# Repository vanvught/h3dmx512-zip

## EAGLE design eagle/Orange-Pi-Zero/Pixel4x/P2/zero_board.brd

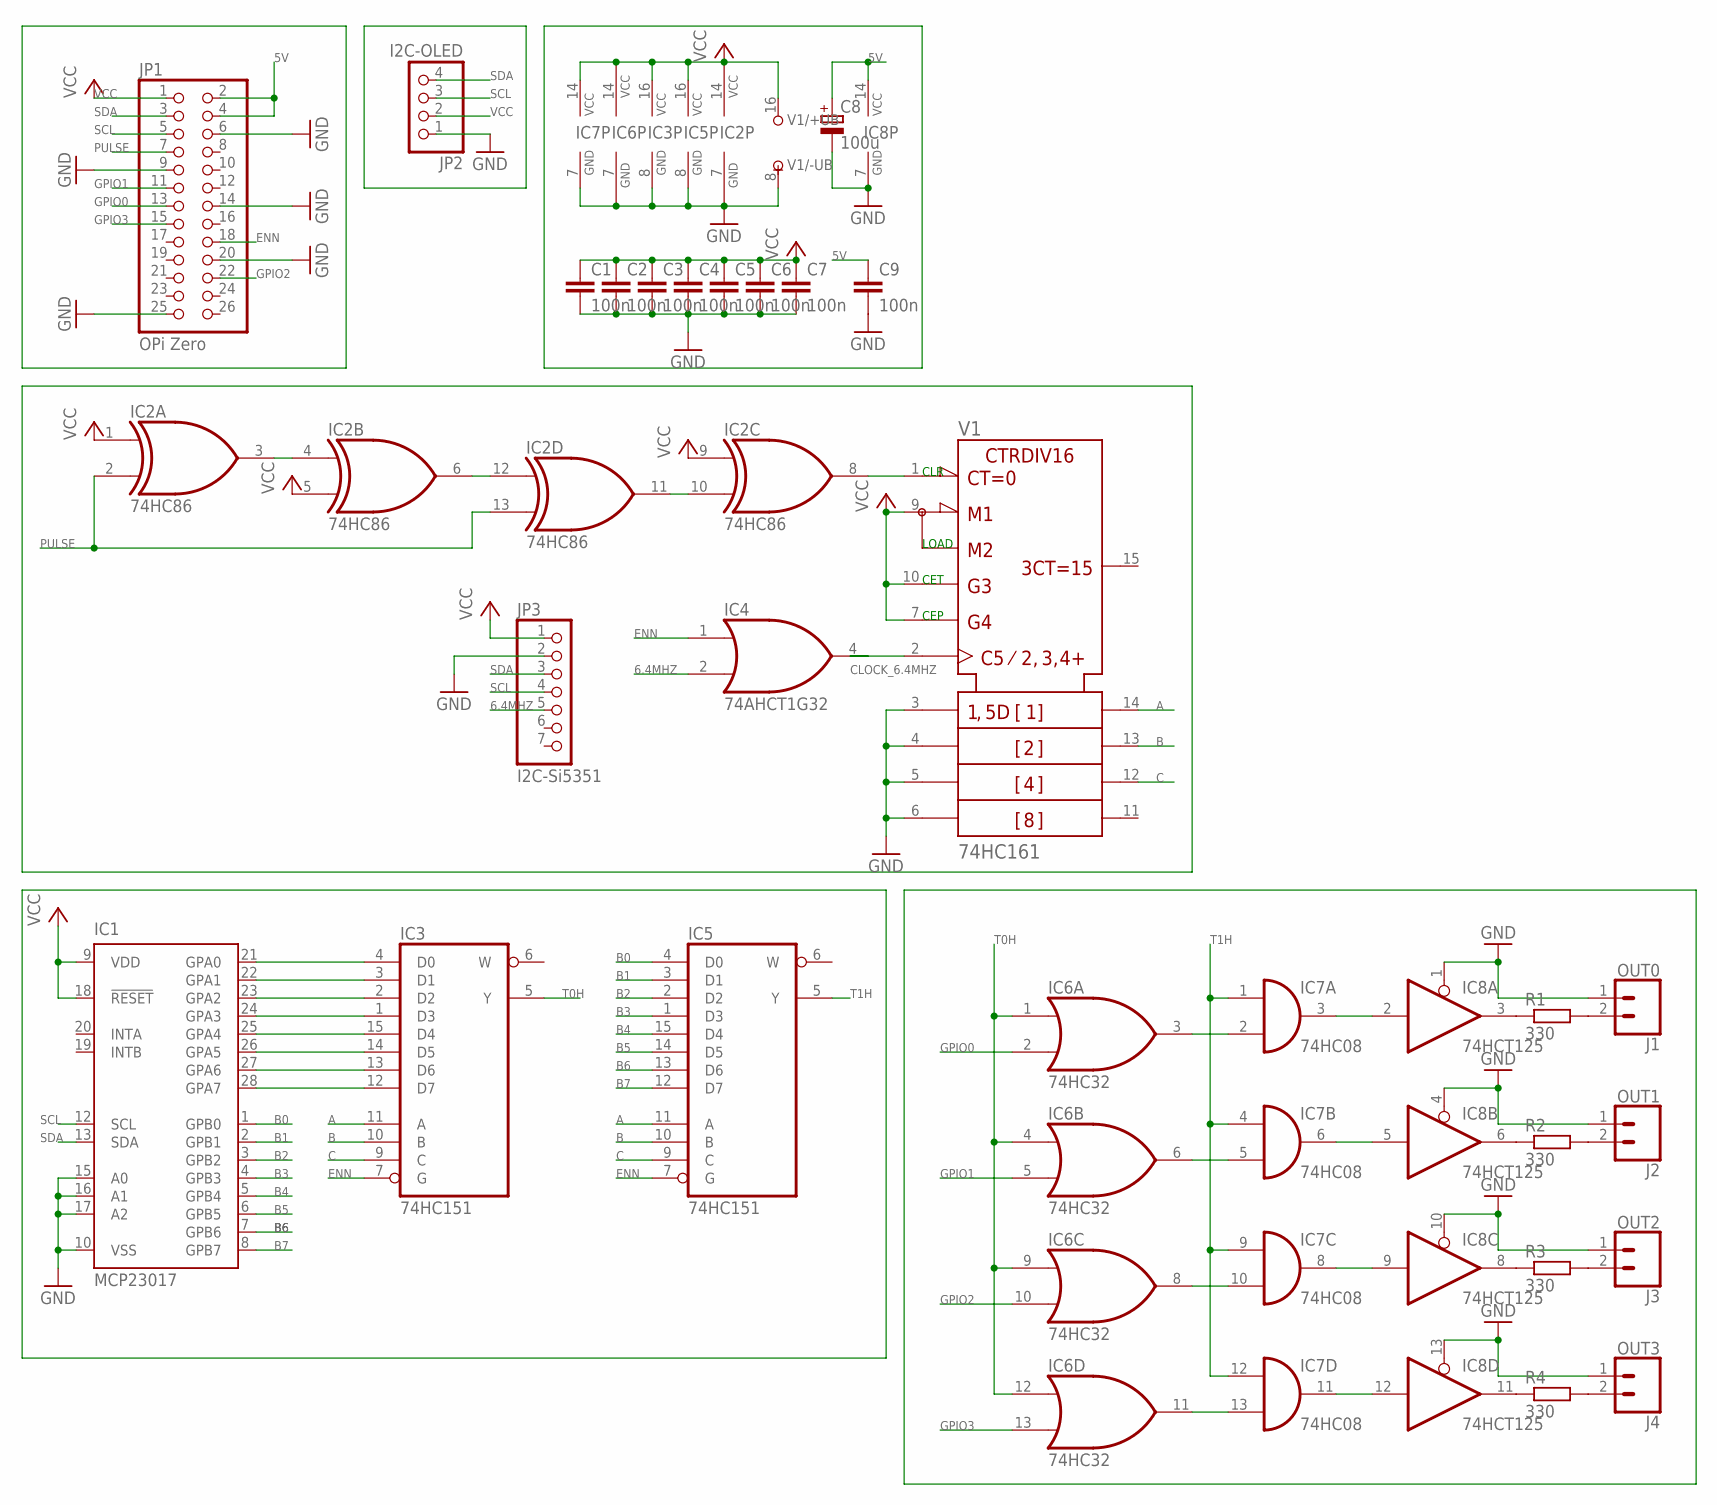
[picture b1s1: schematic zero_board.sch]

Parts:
C1, C2, C3, C4, C5, C6, C7, C9: 100n; C050-024X044
C8: 100u; E2,5-6
IC1: MCP23017; DIL28-3
IC2: 74HC86; DIL14
IC3, IC5: 74HC151; DIL16
IC4: 74AHCT1G32; SOT23-5
IC6: 74HC32; DIL14
IC7: 74HC08; DIL14
IC8: 74HCT125; DIL14
J1: OUT0; SCREWTERMINAL-3.5MM-2
J2: OUT1; SCREWTERMINAL-3.5MM-2
J3: OUT2; SCREWTERMINAL-3.5MM-2
J4: OUT3; SCREWTERMINAL-3.5MM-2
JP1: OPi Zero; 2X13
JP2: I2C-OLED; 1X04
JP3: I2C-Si5351; 1X07
R1, R2, R3, R4: 330; 0204/5
V1: 74HC161; DIL16

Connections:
5V: C8.+, C9.1, IC8.14 (VCC), JP1.2, JP1.4
6.4MHZ: IC4.2 (I1), JP3.5
A: IC3.11 (A), IC5.11 (A), V1.14 (QA)
B: IC3.10 (B), IC5.10 (B), V1.13 (QB)
B0: IC1.1 (GPB0), IC5.4 (D0)
B1: IC1.2 (GPB1), IC5.3 (D1)
B2: IC1.3 (GPB2), IC5.2 (D2)
B3: IC1.4 (GPB3), IC5.1 (D3)
B4: IC1.5 (GPB4), IC5.15 (D4)
B5: IC1.6 (GPB5), IC5.14 (D5)
B6: IC1.7 (GPB6), IC5.13 (D6)
B7: IC1.8 (GPB7), IC5.12 (D7)
C: IC3.9 (C), IC5.9 (C), V1.12 (QC)
CLOCK_6.4MHZ: IC4.4 (O), V1.2 (CLK)
ENN: IC3.7 (G), IC4.1 (I0), IC5.7 (G), JP1.18
GND: C1.2, C2.2, C3.2, C4.2, C5.2, C6.2, C7.2, C8.-, C9.2, IC1.10 (VSS), IC1.15 (A0), IC1.16 (A1), IC1.17 (A2), IC2.7 (GND), IC3.8 (GND), IC4.3 (GND), IC5.8 (GND), IC6.7 (GND), IC7.7 (GND), IC8.1 (OE), IC8.4 (OE), IC8.7 (GND), IC8.10 (OE), IC8.13 (OE), J1.1, J2.1, J3.1, J4.1, JP1.6, JP1.9, JP1.14, JP1.20, JP1.25, JP2.1, JP3.2, V1.3 (A), V1.4 (B), V1.5 (C), V1.6 (D), V1.8 (-UB)
GPIO0: IC6.2 (I1), JP1.13
GPIO1: IC6.5 (I1), JP1.11
GPIO2: IC6.10 (I1), JP1.22
GPIO3: IC6.13 (I1), JP1.15
unnamed: IC2.3 (O), IC2.4 (I0)
unnamed: IC2.6 (O), IC2.12 (I0)
unnamed: IC2.10 (I1), IC2.11 (O)
unnamed: IC2.8 (O), V1.1 (!CLR)
unnamed: IC6.3 (O), IC7.2 (I1)
unnamed: IC6.6 (O), IC7.5 (I1)
unnamed: IC1.21 (GPA0), IC3.4 (D0)
unnamed: IC1.22 (GPA1), IC3.3 (D1)
unnamed: IC1.23 (GPA2), IC3.2 (D2)
unnamed: IC1.24 (GPA3), IC3.1 (D3)
unnamed: IC1.25 (GPA4), IC3.15 (D4)
unnamed: IC1.26 (GPA5), IC3.14 (D5)
unnamed: IC1.27 (GPA6), IC3.13 (D6)
unnamed: IC1.28 (GPA7), IC3.12 (D7)
unnamed: IC6.8 (O), IC7.10 (I1)
unnamed: IC6.11 (O), IC7.13 (I1)
unnamed: IC7.11 (O), IC8.12 (I)
unnamed: IC7.8 (O), IC8.9 (I)
unnamed: IC7.6 (O), IC8.5 (I)
unnamed: IC7.3 (O), IC8.2 (I)
unnamed: IC8.3 (O), R1.1
unnamed: J1.2, R1.2
unnamed: IC8.6 (O), R2.1
unnamed: J2.2, R2.2
unnamed: IC8.8 (O), R3.1
unnamed: J3.2, R3.2
unnamed: IC8.11 (O), R4.1
unnamed: J4.2, R4.2
PULSE: IC2.2 (I1), IC2.13 (I1), JP1.7
SCL: IC1.12 (SCL), JP1.5, JP2.3, JP3.4
SDA: IC1.13 (SDA), JP1.3, JP2.4, JP3.3
T0H: IC3.5 (Y), IC6.1 (I0), IC6.4 (I0), IC6.9 (I0), IC6.12 (I0)
T1H: IC5.5 (Y), IC7.1 (I0), IC7.4 (I0), IC7.9 (I0), IC7.12 (I0)
VCC: C1.1, C2.1, C3.1, C4.1, C5.1, C6.1, C7.1, IC1.9 (VDD), IC1.18 (!RESET), IC2.1 (I0), IC2.5 (I1), IC2.9 (I0), IC2.14 (VCC), IC3.16 (VCC), IC4.5 (VCC), IC5.16 (VCC), IC6.14 (VCC), IC7.14 (VCC), JP1.1, JP2.2, JP3.1, V1.7 (ENP), V1.9 (!LOAD), V1.10 (ENT), V1.16 (+UB)

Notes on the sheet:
CEP
CET
LOAD
CLR

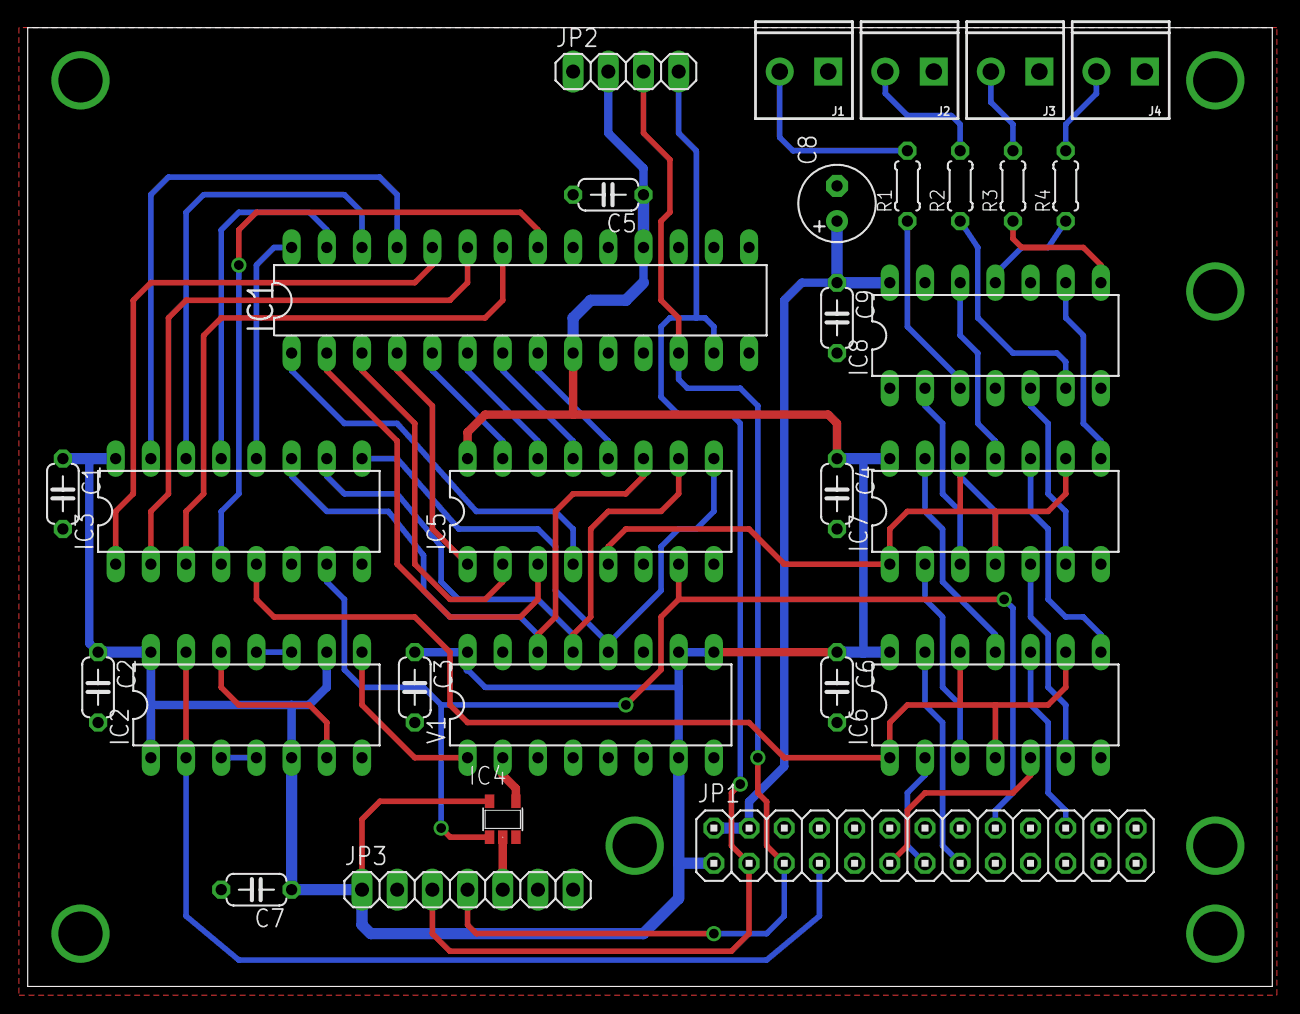
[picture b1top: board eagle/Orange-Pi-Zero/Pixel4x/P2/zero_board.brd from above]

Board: 2 copper layers, 89.8 x 69.2 mm, 29 parts (0 on the bottom side), 54 nets.

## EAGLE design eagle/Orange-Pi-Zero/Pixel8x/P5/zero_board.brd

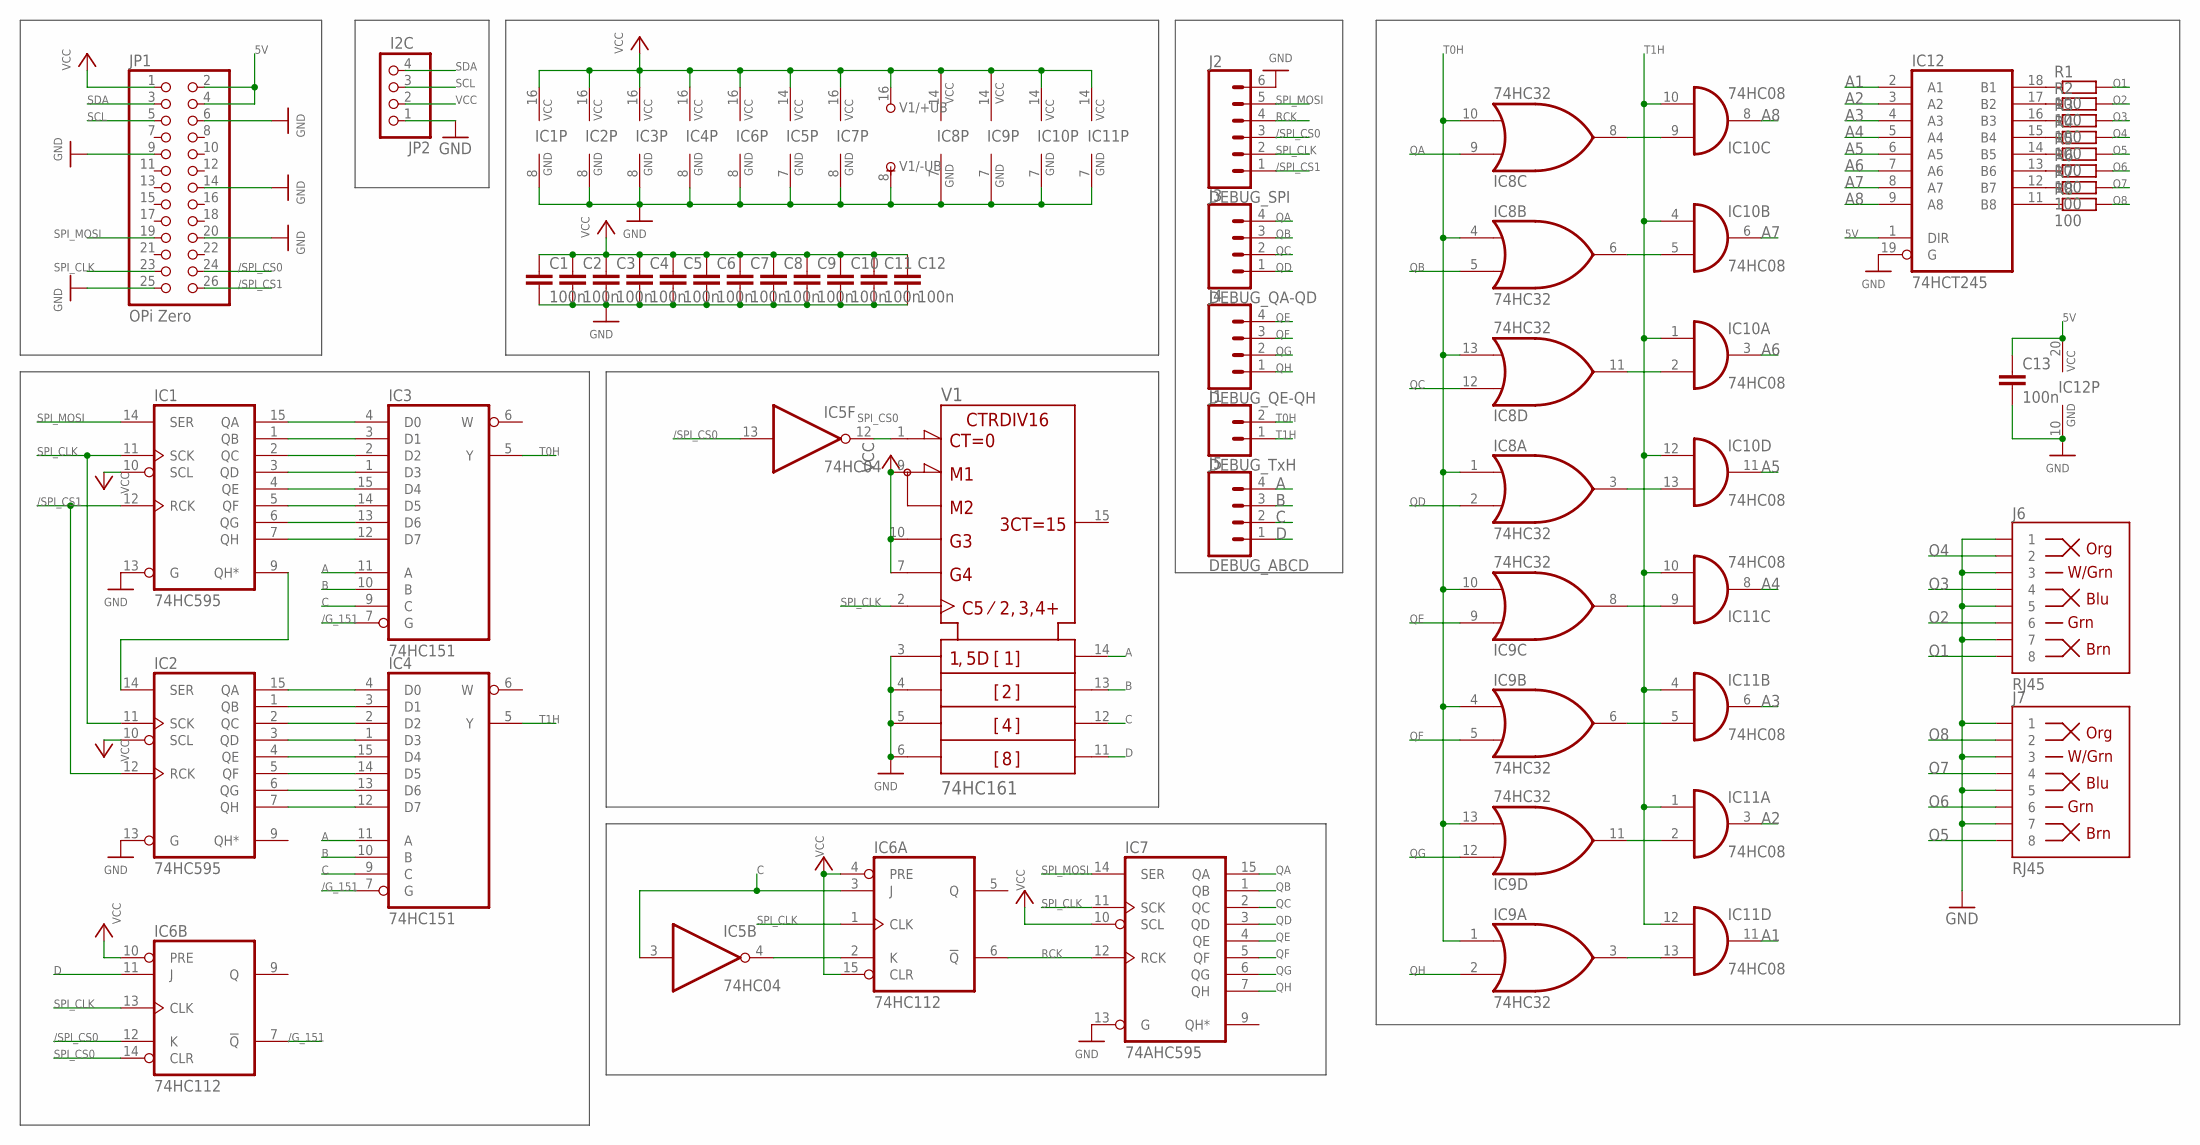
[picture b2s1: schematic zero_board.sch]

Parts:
C1, C2, C3, C4, C5, C6, C7, C8, C9, C10, C11, C12, C13: 100n; C050-024X044
IC1, IC2: 74HC595; DIL16
IC3, IC4: 74HC151; DIL16
IC5: 74HC04; DIL14
IC6: 74HC112; DIL16
IC7: 74AHC595; SO16
IC8, IC9: 74HC32; DIL14
IC10, IC11: 74HC08; DIL14
IC12: 74HCT245; DIL20
J1: DEBUG_TxH; 1X02
J2: DEBUG_SPI; 1X06_LOCK
J3: DEBUG_QA-QD; 1X04_LOCK
J4: DEBUG_QE-QH; 1X04_LOCK
J5: DEBUG_ABCD; 1X04_LOCK
J6, J7: RJ45; RJ45-8
JP1: OPi Zero; 2X13
JP2: I2C; 1X04
R1, R2, R3, R4, R5, R6, R7, R8: 100; 0204/5
V1: 74HC161; DIL16

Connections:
5V: C13.1, IC12.1 (DIR), IC12.20 (VCC), JP1.2, JP1.4
/G_151: IC3.7 (G), IC4.7 (G), IC6.7 (!Q)
/SPI_CS0: IC5.13 (I), IC6.12 (K), J2.3, JP1.24
/SPI_CS1: IC1.12 (RCK), IC2.12 (RCK), J2.1, JP1.26
A: IC3.11 (A), IC4.11 (A), J5.4, V1.14 (QA)
A1: IC11.11 (O), IC12.2 (A1)
A2: IC11.3 (O), IC12.3 (A2)
A3: IC11.6 (O), IC12.4 (A3)
A4: IC11.8 (O), IC12.5 (A4)
A5: IC10.11 (O), IC12.6 (A5)
A6: IC10.3 (O), IC12.7 (A6)
A7: IC10.6 (O), IC12.8 (A7)
A8: IC10.8 (O), IC12.9 (A8)
B: IC3.10 (B), IC4.10 (B), J5.3, V1.13 (QB)
C: IC3.9 (C), IC4.9 (C), IC5.3 (I), IC6.3 (J), J5.2, V1.12 (QC)
D: IC6.11 (J), J5.1, V1.11 (QD)
GND: C1.2, C2.2, C3.2, C4.2, C5.2, C6.2, C7.2, C8.2, C9.2, C10.2, C11.2, C12.2, C13.2, IC1.8 (GND), IC1.13 (G), IC2.8 (GND), IC2.13 (G), IC3.8 (GND), IC4.8 (GND), IC5.7 (GND), IC6.8 (GND), IC7.8 (GND), IC7.13 (G), IC8.7 (GND), IC9.7 (GND), IC10.7 (GND), IC11.7 (GND), IC12.10 (GND), IC12.19 (G), J2.6, J6.1, J6.3, J6.5, J6.7, J7.1, J7.3, J7.5, J7.7, JP1.6, JP1.9, JP1.14, JP1.20, JP1.25, JP2.1, V1.3 (A), V1.4 (B), V1.5 (C), V1.6 (D), V1.8 (-UB)
unnamed: IC9.8 (O), IC11.9 (I0)
unnamed: IC9.6 (O), IC11.5 (I1)
unnamed: IC9.11 (O), IC11.2 (I1)
unnamed: IC9.3 (O), IC11.13 (I1)
unnamed: IC8.8 (O), IC10.9 (I0)
unnamed: IC8.6 (O), IC10.5 (I1)
unnamed: IC8.11 (O), IC10.2 (I1)
unnamed: IC1.15 (QA), IC3.4 (D0)
unnamed: IC1.1 (QB), IC3.3 (D1)
unnamed: IC1.2 (QC), IC3.2 (D2)
unnamed: IC1.3 (QD), IC3.1 (D3)
unnamed: IC5.4 (O), IC6.2 (K)
unnamed: IC8.3 (O), IC10.13 (I1)
unnamed: IC2.15 (QA), IC4.4 (D0)
unnamed: IC1.4 (QE), IC3.15 (D4)
unnamed: IC1.5 (QF), IC3.14 (D5)
unnamed: IC1.6 (QG), IC3.13 (D6)
unnamed: IC1.7 (QH), IC3.12 (D7)
unnamed: IC2.1 (QB), IC4.3 (D1)
unnamed: IC2.2 (QC), IC4.2 (D2)
unnamed: IC2.3 (QD), IC4.1 (D3)
unnamed: IC2.4 (QE), IC4.15 (D4)
unnamed: IC2.5 (QF), IC4.14 (D5)
unnamed: IC2.6 (QG), IC4.13 (D6)
unnamed: IC2.7 (QH), IC4.12 (D7)
unnamed: IC12.18 (B1), R1.1
unnamed: IC12.17 (B2), R2.1
unnamed: IC12.16 (B3), R3.1
unnamed: IC12.15 (B4), R4.1
unnamed: IC12.14 (B5), R5.1
unnamed: IC12.13 (B6), R6.1
unnamed: IC12.12 (B7), R7.1
unnamed: IC12.11 (B8), R8.1
unnamed: IC1.9 (QH*), IC2.14 (SER)
O1: J6.8, R1.2
O2: J6.6, R2.2
O3: J6.4, R3.2
O4: J6.2, R4.2
O5: J7.8, R5.2
O6: J7.6, R6.2
O7: J7.4, R7.2
O8: J7.2, R8.2
QA: IC7.15 (QA), IC8.9 (I0), J3.4
QB: IC7.1 (QB), IC8.5 (I1), J3.3
QC: IC7.2 (QC), IC8.12 (I0), J3.2
QD: IC7.3 (QD), IC8.2 (I1), J3.1
QE: IC7.4 (QE), IC9.9 (I0), J4.4
QF: IC7.5 (QF), IC9.5 (I1), J4.3
QG: IC7.6 (QG), IC9.12 (I0), J4.2
QH: IC7.7 (QH), IC9.2 (I1), J4.1
RCK: IC6.6 (!Q), IC7.12 (RCK), J2.4
SCL: JP1.5, JP2.3
SDA: JP1.3, JP2.4
SPI_CLK: IC1.11 (SCK), IC2.11 (SCK), IC6.1 (CLK), IC6.13 (CLK), IC7.11 (SCK), J2.2, JP1.23, V1.2 (CLK)
SPI_CS0: IC5.12 (O), IC6.14 (CLR), V1.1 (!CLR)
SPI_MOSI: IC1.14 (SER), IC7.14 (SER), J2.5, JP1.19
T0H: IC3.5 (Y), IC8.1 (I0), IC8.4 (I0), IC8.10 (I1), IC8.13 (I1), IC9.1 (I0), IC9.4 (I0), IC9.10 (I1), IC9.13 (I1), J1.2
T1H: IC4.5 (Y), IC10.1 (I0), IC10.4 (I0), IC10.10 (I1), IC10.12 (I0), IC11.1 (I0), IC11.4 (I0), IC11.10 (I1), IC11.12 (I0), J1.1
VCC: C1.1, C2.1, C3.1, C4.1, C5.1, C6.1, C7.1, C8.1, C9.1, C10.1, C11.1, C12.1, IC1.10 (SCL), IC1.16 (VCC), IC2.10 (SCL), IC2.16 (VCC), IC3.16 (VCC), IC4.16 (VCC), IC5.14 (VCC), IC6.4 (PRE), IC6.10 (PRE), IC6.15 (CLR), IC6.16 (VCC), IC7.10 (SCL), IC7.16 (VCC), IC8.14 (VCC), IC9.14 (VCC), IC10.14 (VCC), IC11.14 (VCC), JP1.1, JP2.2, V1.7 (ENP), V1.9 (!LOAD), V1.10 (ENT), V1.16 (+UB)

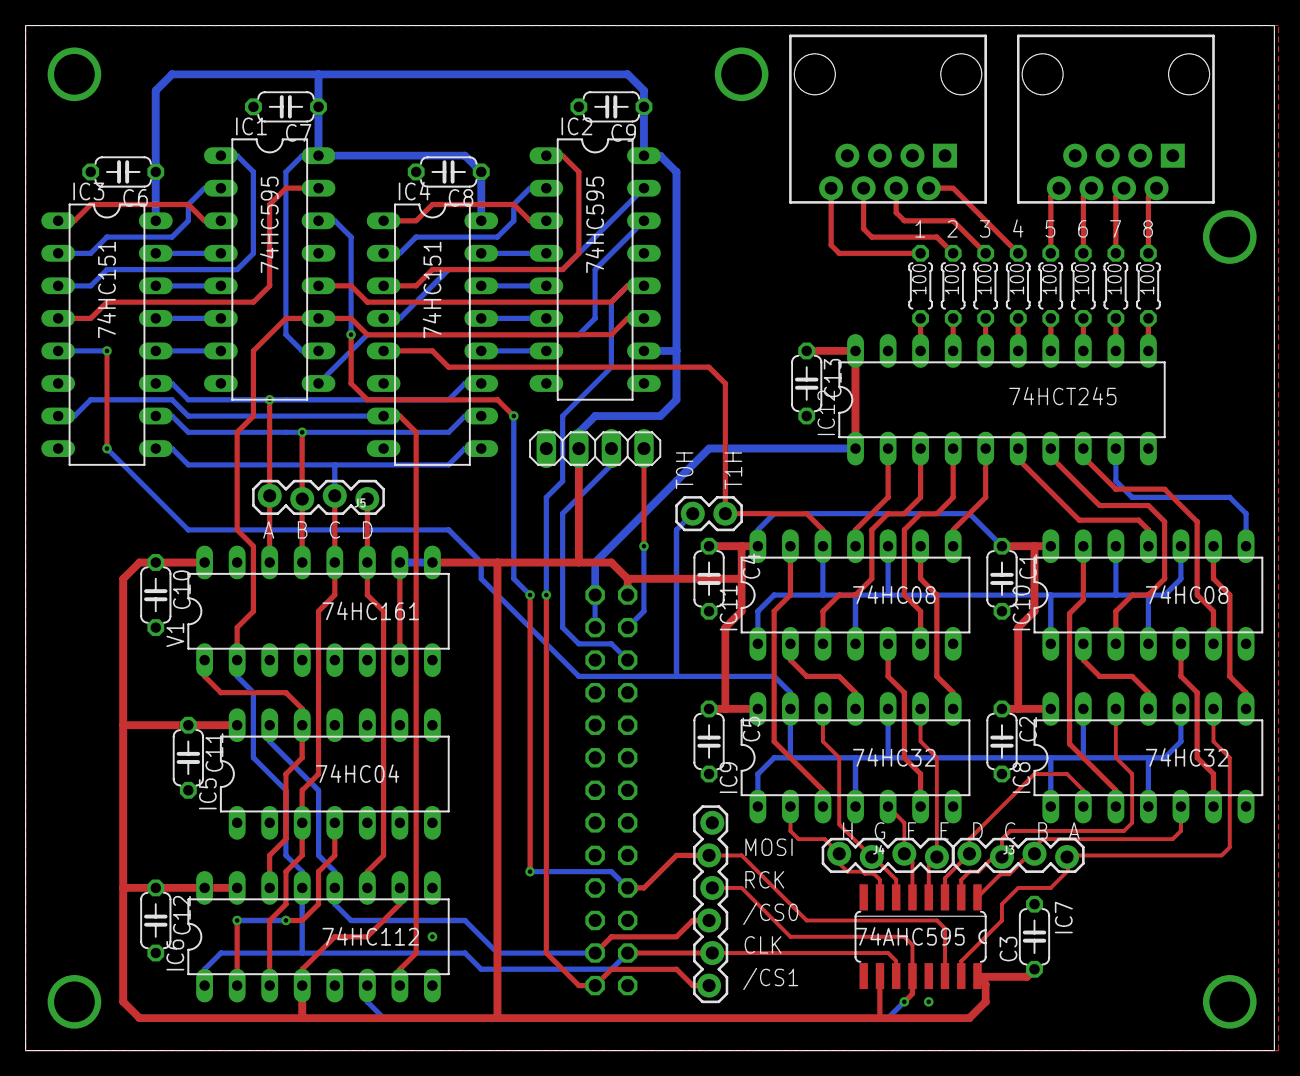
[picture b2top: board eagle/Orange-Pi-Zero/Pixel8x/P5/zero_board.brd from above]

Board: 2 copper layers, 97.5 x 80.0 mm, 43 parts (1 on the bottom side), 76 nets.

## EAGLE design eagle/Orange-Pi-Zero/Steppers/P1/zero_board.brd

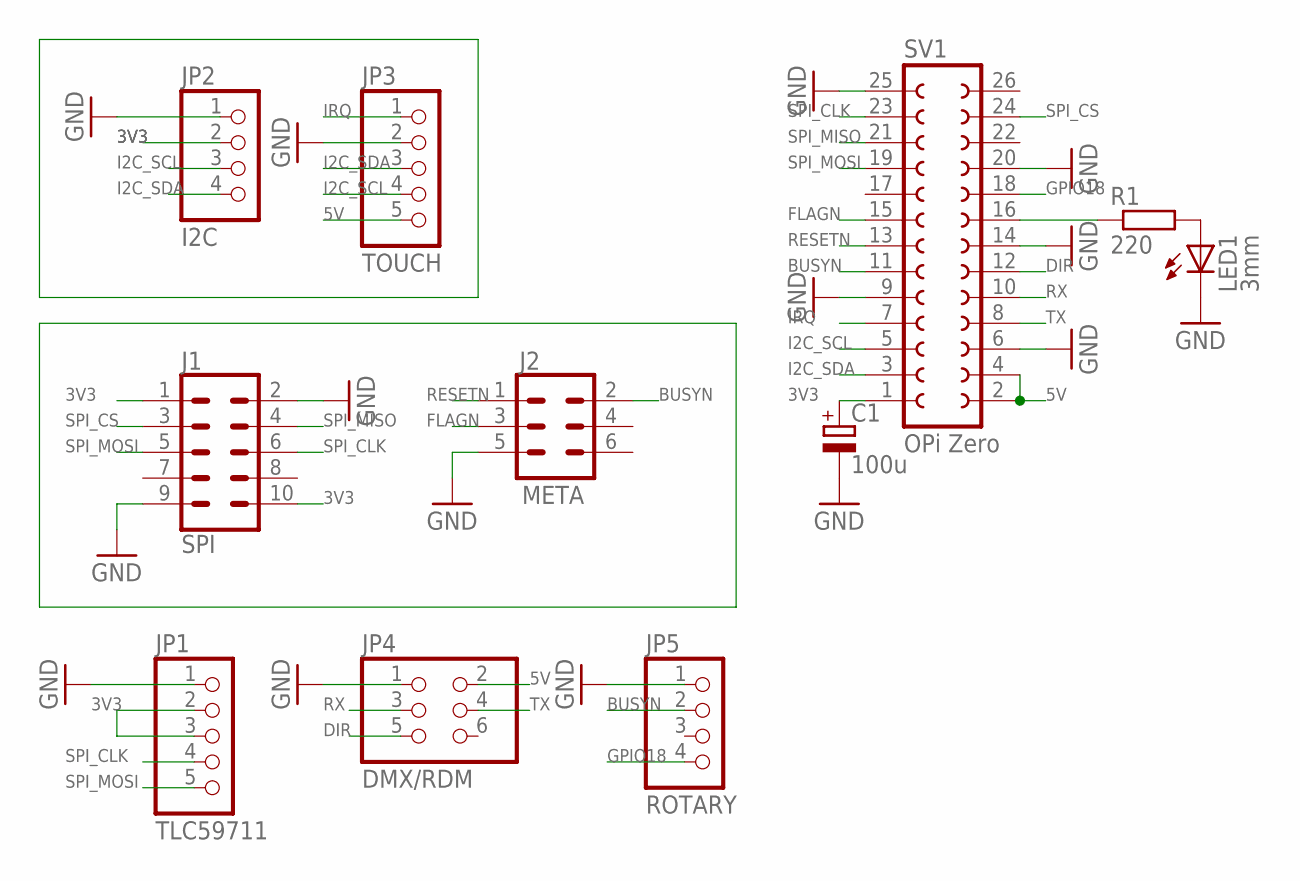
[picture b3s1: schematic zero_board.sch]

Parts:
C1: 100u; E2,5-6
J1: SPI; 2X5-SHROUDED
J2: META; 2X3-SHROUDED
JP1: TLC59711; 1X05
JP2: I2C; 1X04
JP3: TOUCH; 1X05
JP4: DMX/RDM; 2X03
JP5: ROTARY; 1X04
LED1: 3mm; LED3MM
R1: 220; 0204V
SV1: OPi Zero; FE13-2

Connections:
3V3: C1.+, J1.1, J1.10, JP1.2, JP1.3, JP2.2, SV1.1
5V: JP3.5, JP4.2, SV1.2, SV1.4
BUSYN: J2.2, JP5.2, SV1.11
DIR: JP4.5, SV1.12
FLAGN: J2.3, SV1.15
GND: C1.-, J1.2, J1.9, J2.5, JP1.1, JP2.1, JP3.2, JP4.1, JP5.1, LED1.K (C), SV1.6, SV1.9, SV1.14, SV1.20, SV1.25
GPIO18: JP5.4, SV1.18
I2C_SCL: JP2.3, JP3.4, SV1.5
I2C_SDA: JP2.4, JP3.3, SV1.3
IRQ: JP3.1, SV1.7
unnamed: LED1.A, R1.2
unnamed: R1.1, SV1.16
RESETN: J2.1, SV1.13
RX: JP4.3, SV1.10
SPI_CLK: J1.6, JP1.4, SV1.23
SPI_CS: J1.3, SV1.24
SPI_MISO: J1.4, SV1.21
SPI_MOSI: J1.5, JP1.5, SV1.19
TX: JP4.4, SV1.8

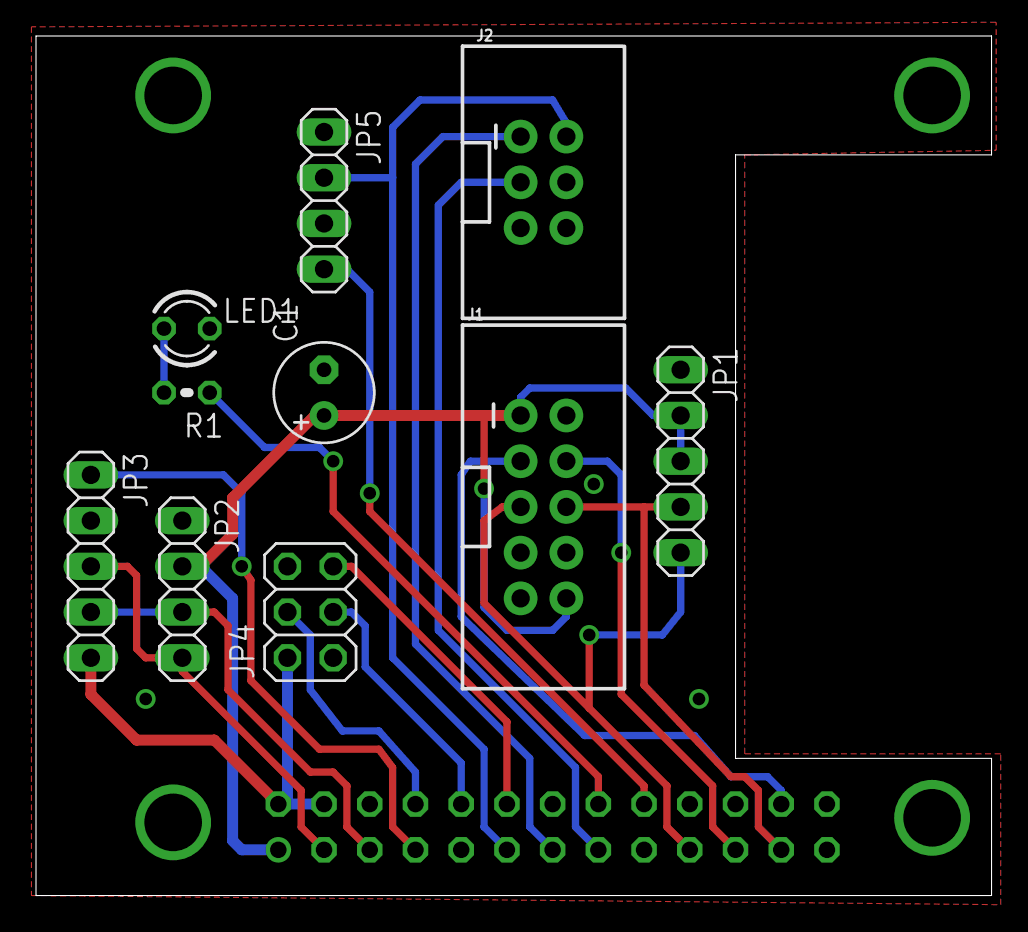
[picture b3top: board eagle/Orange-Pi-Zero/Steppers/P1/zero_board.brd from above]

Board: 2 copper layers, 53.1 x 47.8 mm, 11 parts (1 on the bottom side), 19 nets.

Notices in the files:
parts and their libraries:
SparkFun-Connectors: Licensing: Creative Commons ShareAlike 4.0 International - https://creativecommons.org/licenses/by-sa/4.0
microbuilder: This work is placed in the public domain, and may be freely used for commercial and non-commercial work with the following conditions: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
